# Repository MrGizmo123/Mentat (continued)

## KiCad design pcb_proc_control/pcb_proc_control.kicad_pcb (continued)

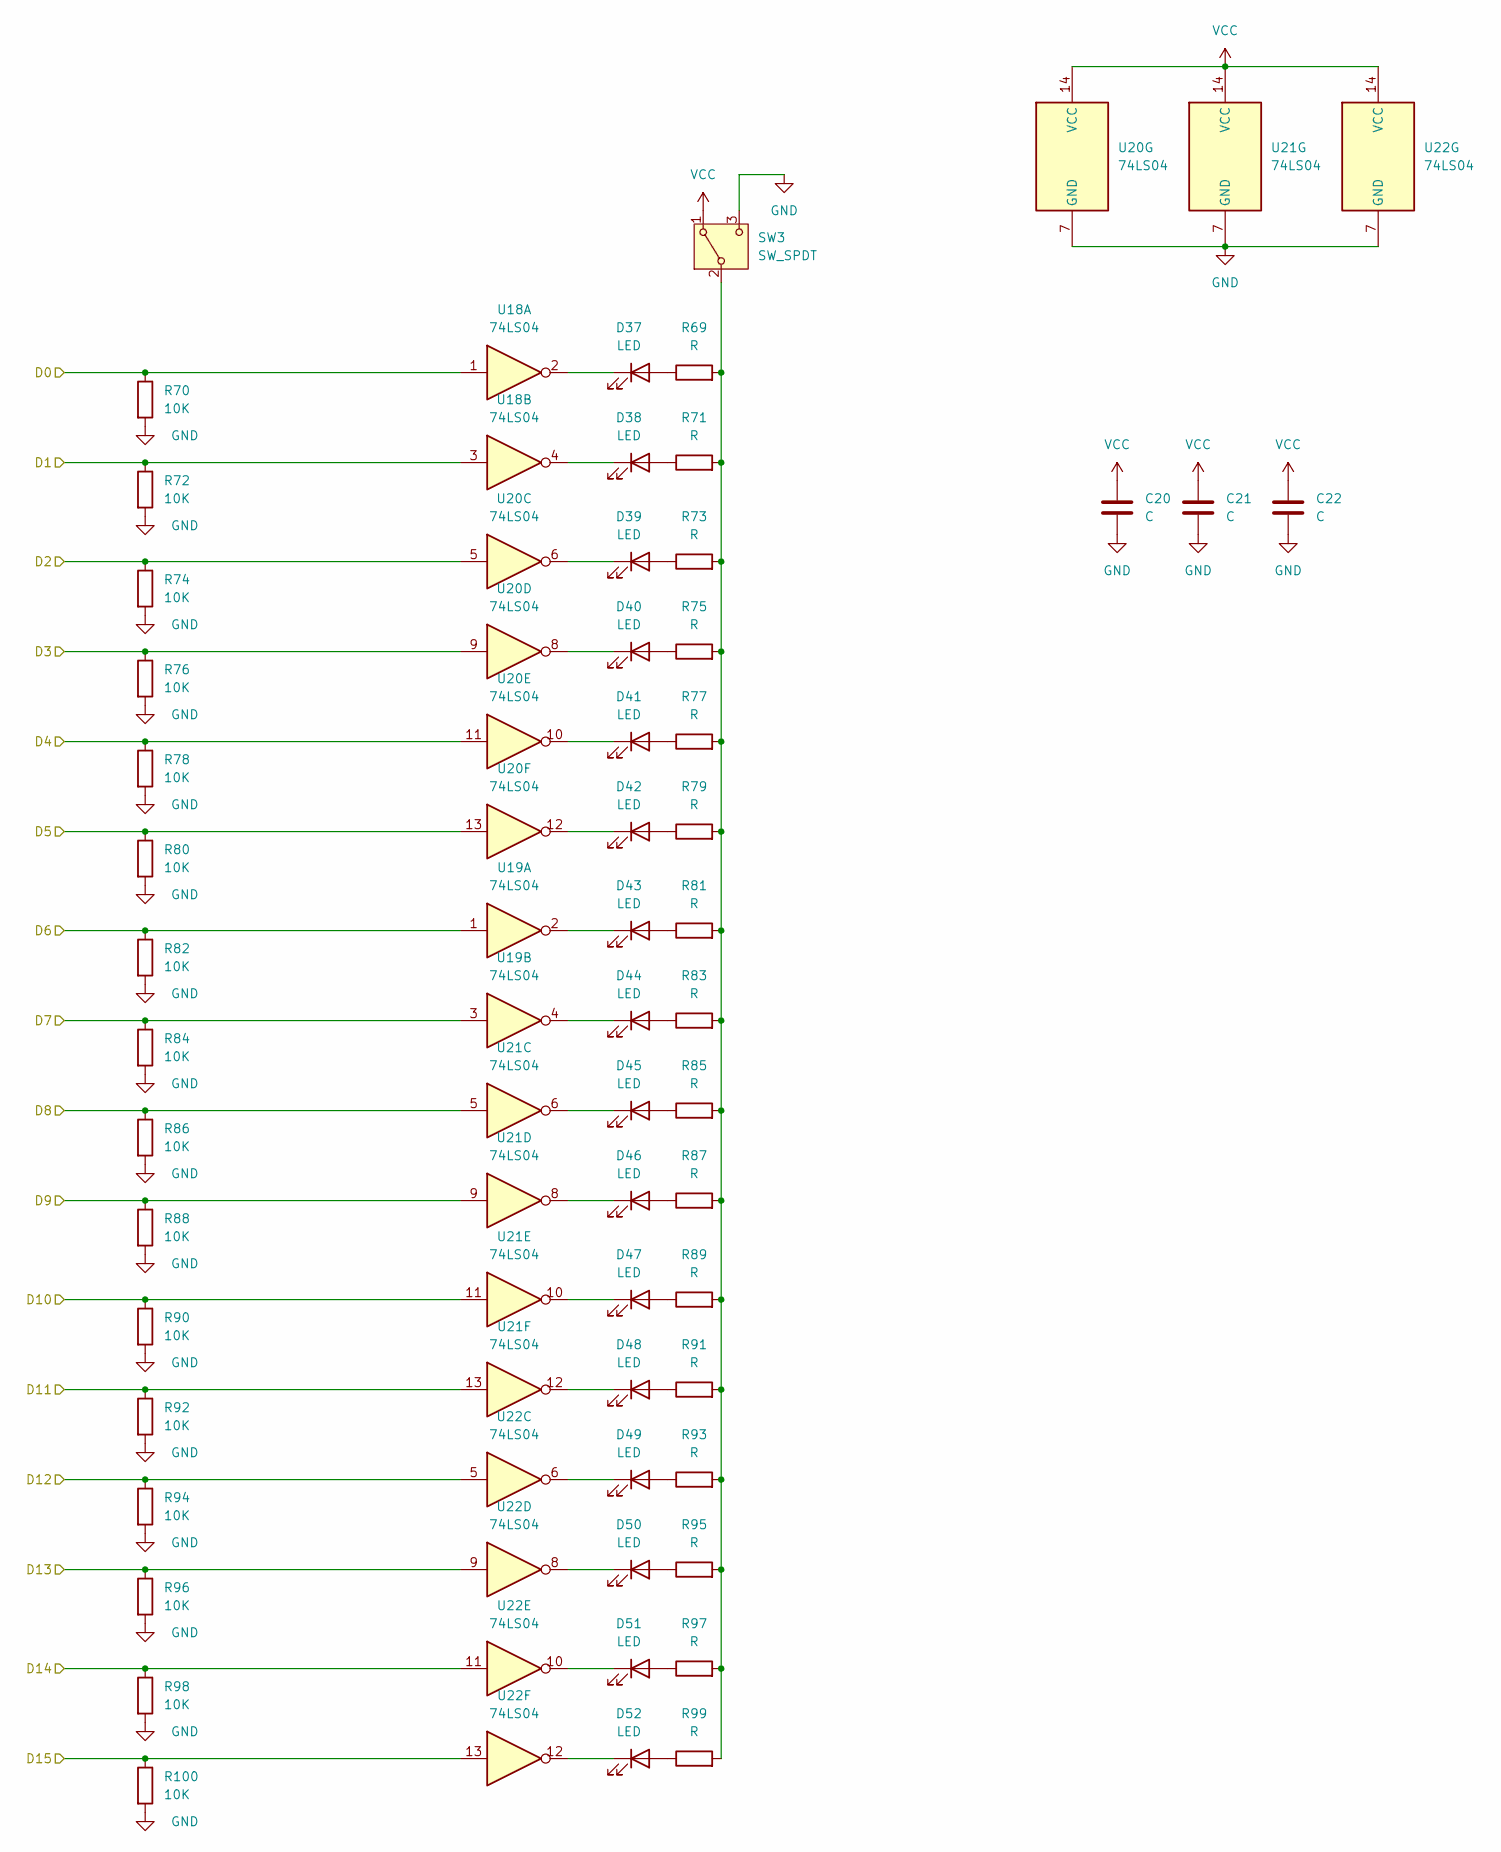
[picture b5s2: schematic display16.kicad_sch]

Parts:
C20, C21, C22: C; C_0805_2012Metric
D37, D38, D39, D40, D41, D42, D43, D44, D45, D46, D47, D48, D49, D50, D51, D52: LED; LED_Rectangular_W5.0mm_H2.0mm
R69, R71, R73, R75, R77, R79, R81, R83, R85, R87, R89, R91, R93, R95, R97, R99: R; R_0805_2012Metric
R70, R72, R74, R76, R78, R80, R82, R84, R86, R88, R90, R92, R94, R96, R98, R100: 10K; R_0805_2012Metric
SW3: SW_SPDT; SW_E-Switch_EG1271_SPDT
U18, U19, U20, U21, U22: 74LS04; DIP-14_W7.62mm_Socket_LongPads

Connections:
/Display3/D0: R70.1, U18.1; also elsewhere on the board
/Display3/D1: R72.1, U18.3; also elsewhere on the board
/Display3/D2: R74.1, U20.5; also elsewhere on the board
/Display3/D3: R76.1, U20.9; also elsewhere on the board
/Display3/D4: R78.1, U20.11; also elsewhere on the board
/Display3/D5: R80.1, U20.13; also elsewhere on the board
/Display3/D6: R82.1, U19.1; also elsewhere on the board
/Display3/D7: R84.1, U19.3; also elsewhere on the board
/Display3/D8: R86.1, U21.5; also elsewhere on the board
/Display3/D9: R88.1, U21.9; also elsewhere on the board
/Display3/D10: R90.1, U21.11; also elsewhere on the board
/Display3/D11: R92.1, U21.13; also elsewhere on the board
/Display3/D12: R94.1, U22.5
/Display3/D13: R96.1, U22.9
/Display3/D14: R98.1, U22.11
/Display3/D15: R100.1, U22.13
/Display4/D8: U18.5; also elsewhere on the board
/Display4/D9: U18.9; also elsewhere on the board
/Display4/D10: U18.11; also elsewhere on the board
/Display4/D11: U18.13; also elsewhere on the board
/Display4/D12: U19.5; also elsewhere on the board
/Display4/D13: U19.9; also elsewhere on the board
/Display4/D14: U19.11; also elsewhere on the board
/Display4/D15: U19.13; also elsewhere on the board
GND: C20.2, C21.2, C22.2, R70.2, R72.2, R74.2, R76.2, R78.2, R80.2, R82.2, R84.2, R86.2, R88.2, R90.2, R92.2, R94.2, R96.2, R98.2, R100.2, SW3.3 (C), U18.7 (GND), U19.7 (GND), U20.7 (GND), U21.7 (GND), U22.7 (GND); also elsewhere on the board
unnamed 106: U18.6; also elsewhere on the board
unnamed 108: U18.8; also elsewhere on the board
unnamed 110: U18.10; also elsewhere on the board
unnamed 112: U18.12; also elsewhere on the board
unnamed 114: U19.6; also elsewhere on the board
unnamed 116: U19.8; also elsewhere on the board
unnamed 118: U19.10; also elsewhere on the board
unnamed 120: U19.12; also elsewhere on the board
unnamed: D37.2 (A), R69.1
unnamed: D37.1 (K), U18.2
unnamed: D38.2 (A), R71.1
unnamed: D38.1 (K), U18.4
unnamed: D39.2 (A), R73.1
unnamed: D39.1 (K), U20.6
unnamed: D40.2 (A), R75.1
unnamed: D40.1 (K), U20.8
unnamed: D41.2 (A), R77.1
unnamed: D41.1 (K), U20.10
unnamed: D42.2 (A), R79.1
unnamed: D42.1 (K), U20.12
unnamed: D43.2 (A), R81.1
unnamed: D43.1 (K), U19.2
unnamed: D44.2 (A), R83.1
unnamed: D44.1 (K), U19.4
unnamed: D45.2 (A), R85.1
unnamed: D45.1 (K), U21.6
unnamed: D46.2 (A), R87.1
unnamed: D46.1 (K), U21.8
unnamed: D47.2 (A), R89.1
unnamed: D47.1 (K), U21.10
unnamed: D48.2 (A), R91.1
unnamed: D48.1 (K), U21.12
unnamed: D49.2 (A), R93.1
unnamed: D49.1 (K), U22.6
unnamed: D50.2 (A), R95.1
unnamed: D50.1 (K), U22.8
unnamed: D51.2 (A), R97.1
unnamed: D51.1 (K), U22.10
unnamed: D52.2 (A), R99.1
unnamed: D52.1 (K), U22.12
unnamed: R69.2, R71.2, R73.2, R75.2, R77.2, R79.2, R81.2, R83.2, R85.2, R87.2, R89.2, R91.2, R93.2, R95.2, R97.2, R99.2, SW3.2 (B)
VCC: C20.1, C21.1, C22.1, SW3.1 (A), U18.14 (VCC), U19.14 (VCC), U20.14 (VCC), U21.14 (VCC), U22.14 (VCC); also elsewhere on the board

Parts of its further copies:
C14, C15, C16, C17, C18, C19: C; C_0805_2012Metric
D5, D6, D7, D8, D9, D10, D11, D12, D13, D14, D15, D16, D17, D18, D19, D20, D21, D22, D23, D24, D25, D26, D27, D28, D29, D30, D31, D32, D33, D34, D35, D36: LED; LED_Rectangular_W5.0mm_H2.0mm
R5, R7, R9, R11, R13, R15, R17, R19, R21, R23, R25, R27, R29, R31, R33, R35, R37, R39, R41, R43, R45, R47, R49, R51, R53, R55, R57, R59, R61, R63, R65, R67: R; R_0805_2012Metric
R6, R8, R10, R12, R14, R16, R18, R20, R22, R24, R26, R28, R30, R32, R34, R36, R38, R40, R42, R44, R46, R48, R50, R52, R54, R56, R58, R60, R62, R64, R66, R68: 10K; R_0805_2012Metric
SW1, SW2: SW_SPDT; SW_E-Switch_EG1271_SPDT
U14, U15, U16, U17: 74LS04; DIP-14_W7.62mm_Socket_LongPads

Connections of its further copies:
/Display1/D0: R6.1, U14.1; also elsewhere on the board
/Display1/D1: R8.1, U14.3; also elsewhere on the board
/Display1/D2: R10.1, U14.5; also elsewhere on the board
/Display1/D3: R12.1, U14.9; also elsewhere on the board
/Display1/D4: R14.1, U14.11; also elsewhere on the board
/Display1/D5: R16.1, U14.13; also elsewhere on the board
/Display1/D6: R18.1, U15.1; also elsewhere on the board
/Display1/D7: R20.1, U15.3; also elsewhere on the board
/Display1/D8: R22.1, U15.5; also elsewhere on the board
/Display1/D9: R24.1, U15.9; also elsewhere on the board
/Display1/D10: R26.1, U15.11; also elsewhere on the board
/Display1/D11: R28.1, U15.13; also elsewhere on the board
/Display1/D12: R30.1, U16.5; also elsewhere on the board
/Display1/D13: R32.1, U16.9; also elsewhere on the board
/Display1/D14: R34.1, U16.11; also elsewhere on the board
/Display1/D15: R36.1, U16.13; also elsewhere on the board
/Display4/D0: R38.1, U16.1; also elsewhere on the board
/Display4/D1: R40.1, U16.3; also elsewhere on the board
/Display4/D2: R42.1, U17.5; also elsewhere on the board
/Display4/D3: R44.1, U17.9; also elsewhere on the board
/Display4/D4: R46.1, U17.11; also elsewhere on the board
/Display4/D5: R48.1, U17.13; also elsewhere on the board
/Display4/D6: R50.1, U17.1; also elsewhere on the board
/Display4/D7: R52.1, U17.3; also elsewhere on the board
/Display4/D8: R54.1; also elsewhere on the board
/Display4/D9: R56.1; also elsewhere on the board
/Display4/D10: R58.1; also elsewhere on the board
/Display4/D11: R60.1; also elsewhere on the board
/Display4/D12: R62.1; also elsewhere on the board
/Display4/D13: R64.1; also elsewhere on the board
/Display4/D14: R66.1; also elsewhere on the board
/Display4/D15: R68.1; also elsewhere on the board
GND: C14.2, C15.2, C16.2, C17.2, C18.2, C19.2, R6.2, R8.2, R10.2, R12.2, R14.2, R16.2, R18.2, R20.2, R22.2, R24.2, R26.2, R28.2, R30.2, R32.2, R34.2, R36.2, R38.2, R40.2, R42.2, R44.2, R46.2, R48.2, R50.2, R52.2, R54.2, R56.2, R58.2, R60.2, R62.2, R64.2, R66.2, R68.2, SW1.3 (C), SW2.3 (C), U14.7 (GND), U15.7 (GND), U16.7 (GND), U17.7 (GND); also elsewhere on the board
unnamed: D5.2 (A), R5.1
unnamed: D5.1 (K), U14.2
unnamed: D6.2 (A), R7.1
unnamed: D6.1 (K), U14.4
unnamed: D7.2 (A), R9.1
unnamed: D7.1 (K), U14.6
unnamed: D8.2 (A), R11.1
unnamed: D8.1 (K), U14.8
unnamed: D9.2 (A), R13.1
unnamed: D9.1 (K), U14.10
unnamed: D10.2 (A), R15.1
unnamed: D10.1 (K), U14.12
unnamed: D11.2 (A), R17.1
unnamed: D11.1 (K), U15.2
unnamed: D12.2 (A), R19.1
unnamed: D12.1 (K), U15.4
unnamed: D13.2 (A), R21.1
unnamed: D13.1 (K), U15.6
unnamed: D14.2 (A), R23.1
unnamed: D14.1 (K), U15.8
unnamed: D15.2 (A), R25.1
unnamed: D15.1 (K), U15.10
unnamed: D16.2 (A), R27.1
unnamed: D16.1 (K), U15.12
unnamed: D17.2 (A), R29.1
unnamed: D17.1 (K), U16.6
unnamed: D18.2 (A), R31.1
unnamed: D18.1 (K), U16.8
unnamed: D19.2 (A), R33.1
unnamed: D19.1 (K), U16.10
unnamed: D20.2 (A), R35.1
unnamed: D20.1 (K), U16.12
unnamed: D21.2 (A), R37.1
unnamed: D21.1 (K), U16.2
unnamed: D22.2 (A), R39.1
unnamed: D22.1 (K), U16.4
unnamed: D23.2 (A), R41.1
unnamed: D23.1 (K), U17.6
unnamed: D24.2 (A), R43.1
unnamed: D24.1 (K), U17.8
unnamed: D25.2 (A), R45.1
unnamed: D25.1 (K), U17.10
unnamed: D26.2 (A), R47.1
unnamed: D26.1 (K), U17.12
unnamed: D27.2 (A), R49.1
unnamed: D27.1 (K), U17.2
unnamed: D28.2 (A), R51.1
unnamed: D28.1 (K), U17.4
unnamed: D29.2 (A), R53.1
unnamed 106: D29.1 (K); also elsewhere on the board
unnamed: D30.2 (A), R55.1
unnamed 108: D30.1 (K); also elsewhere on the board
unnamed: D31.2 (A), R57.1
unnamed 110: D31.1 (K); also elsewhere on the board
unnamed: D32.2 (A), R59.1
unnamed 112: D32.1 (K); also elsewhere on the board
unnamed: D33.2 (A), R61.1
unnamed 114: D33.1 (K); also elsewhere on the board
unnamed: D34.2 (A), R63.1
unnamed 116: D34.1 (K); also elsewhere on the board
unnamed: D35.2 (A), R65.1
unnamed 118: D35.1 (K); also elsewhere on the board
unnamed: D36.2 (A), R67.1
unnamed 120: D36.1 (K); also elsewhere on the board
unnamed: R5.2, R7.2, R9.2, R11.2, R13.2, R15.2, R17.2, R19.2, R21.2, R23.2, R25.2, R27.2, R29.2, R31.2, R33.2, R35.2, SW1.2 (B)
unnamed: R37.2, R39.2, R41.2, R43.2, R45.2, R47.2, R49.2, R51.2, R53.2, R55.2, R57.2, R59.2, R61.2, R63.2, R65.2, R67.2, SW2.2 (B)
VCC: C14.1, C15.1, C16.1, C17.1, C18.1, C19.1, SW1.1 (A), SW2.1 (A), U14.14 (VCC), U15.14 (VCC), U16.14 (VCC), U17.14 (VCC); also elsewhere on the board

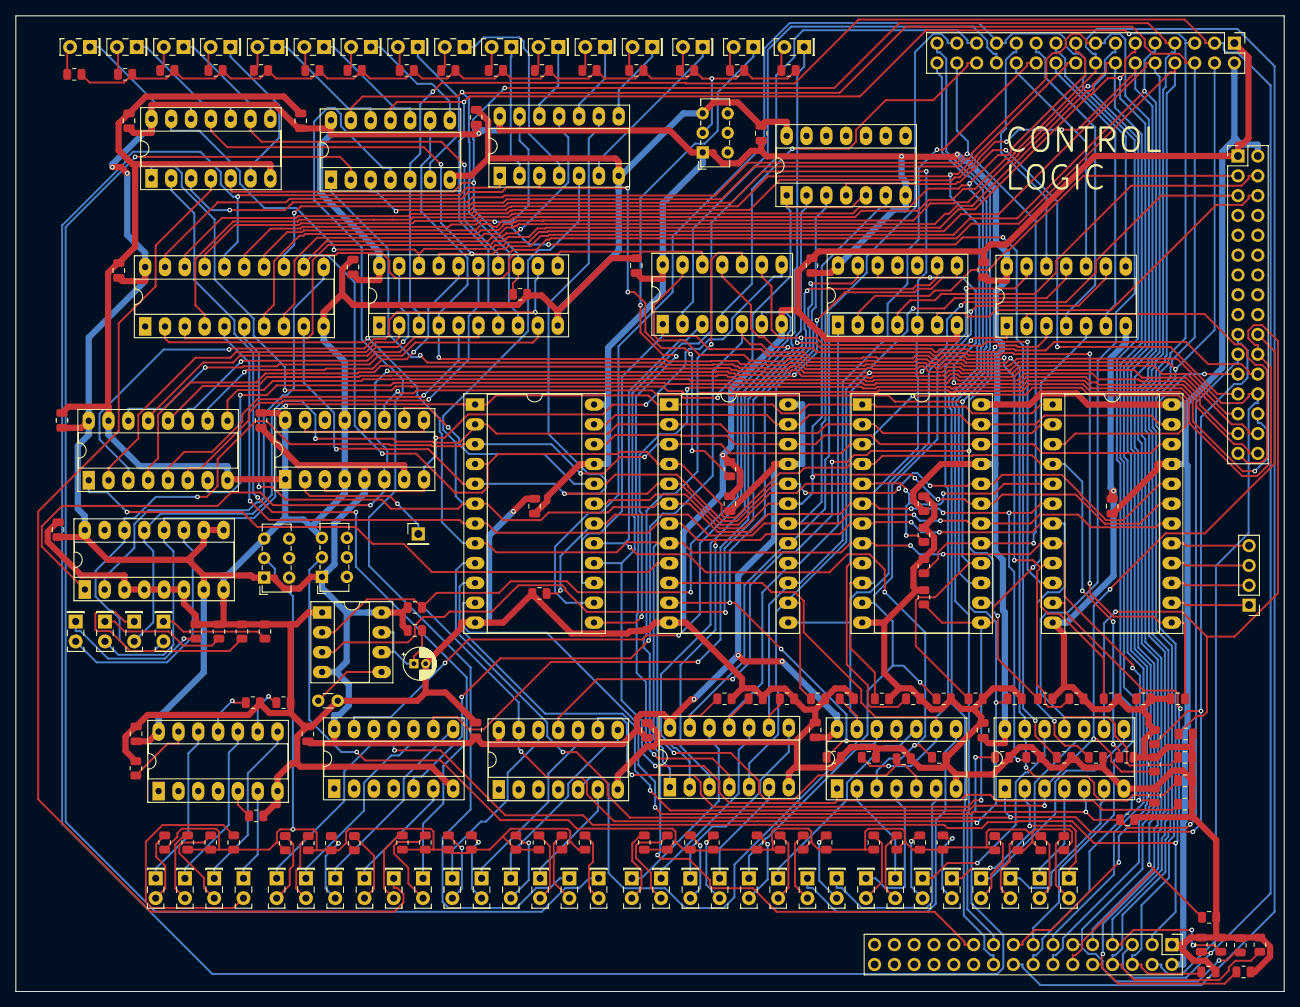
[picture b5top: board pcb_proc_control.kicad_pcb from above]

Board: 2 copper layers, 162.5 x 125.0 mm, 210 parts (0 on the bottom side), 212 nets.

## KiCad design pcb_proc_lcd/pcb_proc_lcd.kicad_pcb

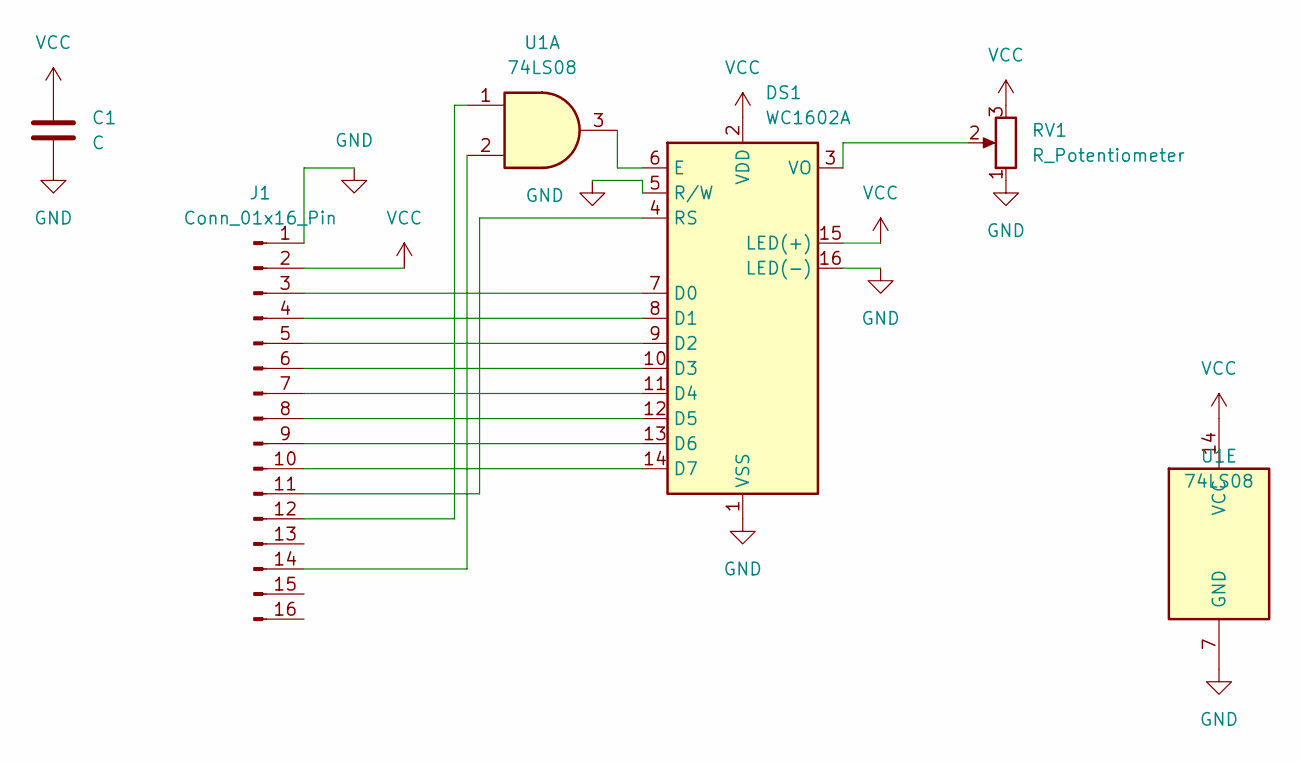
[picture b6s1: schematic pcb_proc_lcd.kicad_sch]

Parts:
C1: C; C_0805_2012Metric
DS1: WC1602A
J1: Conn_01x16_Pin; PinHeader_1x16_P2.54mm_Vertical
RV1: R_Potentiometer; Potentiometer_Vishay_T93YA_Vertical
U1: 74LS08; DIP-14_W7.62mm_Socket_LongPads

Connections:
GND: C1.2, DS1.1 (VSS), DS1.5 (R/W), DS1.16 (LED(-)), J1.1, RV1.1, U1.7 (GND)
unnamed: DS1.7 (D0), J1.3
unnamed: DS1.8 (D1), J1.4
unnamed: DS1.9 (D2), J1.5
unnamed: DS1.10 (D3), J1.6
unnamed: DS1.11 (D4), J1.7
unnamed: DS1.12 (D5), J1.8
unnamed: DS1.13 (D6), J1.9
unnamed: DS1.14 (D7), J1.10
unnamed: DS1.6 (E), U1.3
unnamed: DS1.4 (RS), J1.11
unnamed: DS1.3 (VO), RV1.2
unnamed: J1.12, U1.1
unnamed: J1.14, U1.2
VCC: C1.1, DS1.2 (VDD), DS1.15 (LED(+)), J1.2, RV1.3, U1.14 (VCC)

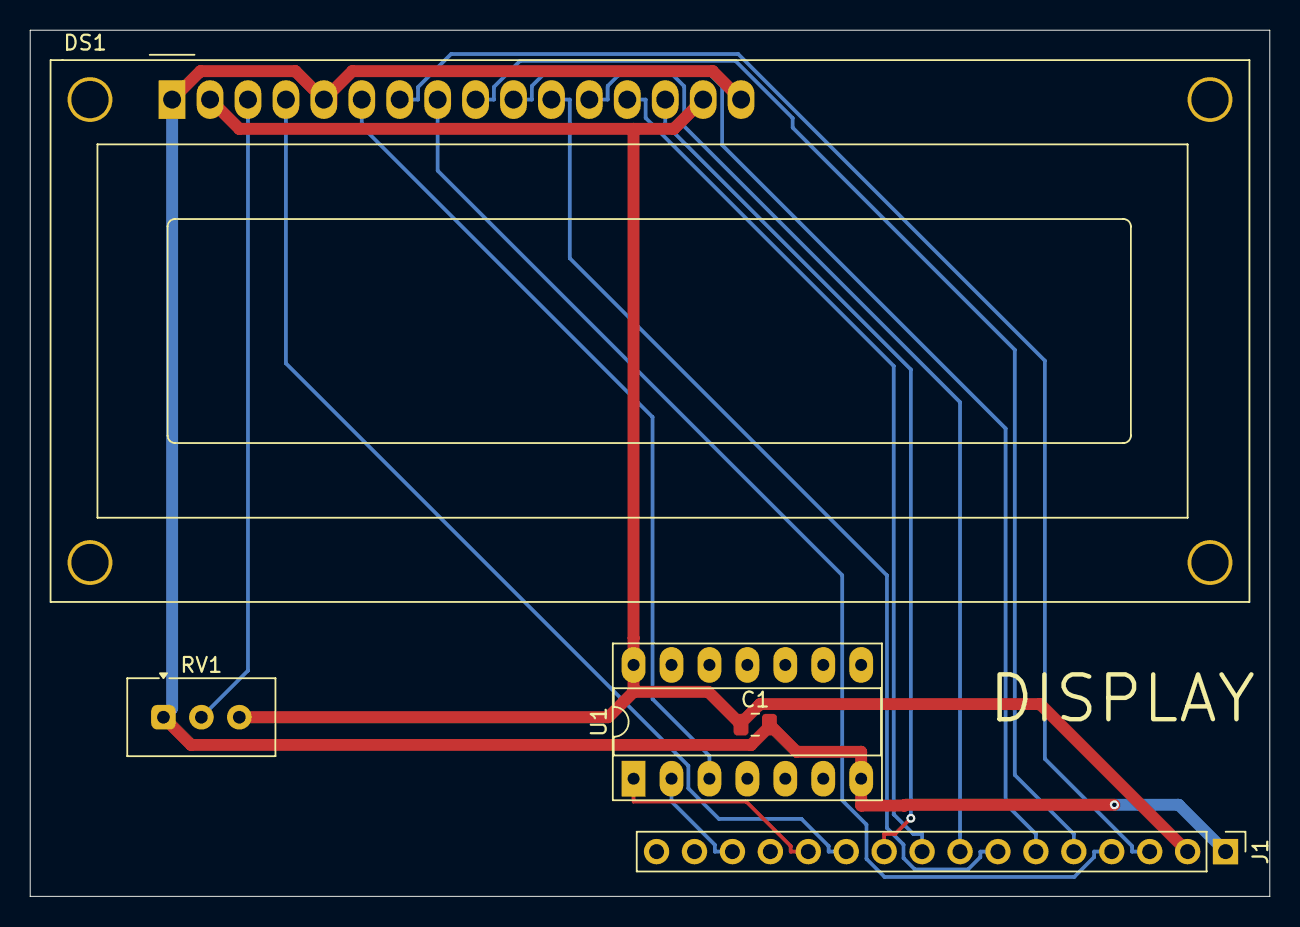
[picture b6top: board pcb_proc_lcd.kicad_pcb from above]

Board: 2 copper layers, 83.0 x 58.0 mm, 5 parts (0 on the bottom side), 15 nets.

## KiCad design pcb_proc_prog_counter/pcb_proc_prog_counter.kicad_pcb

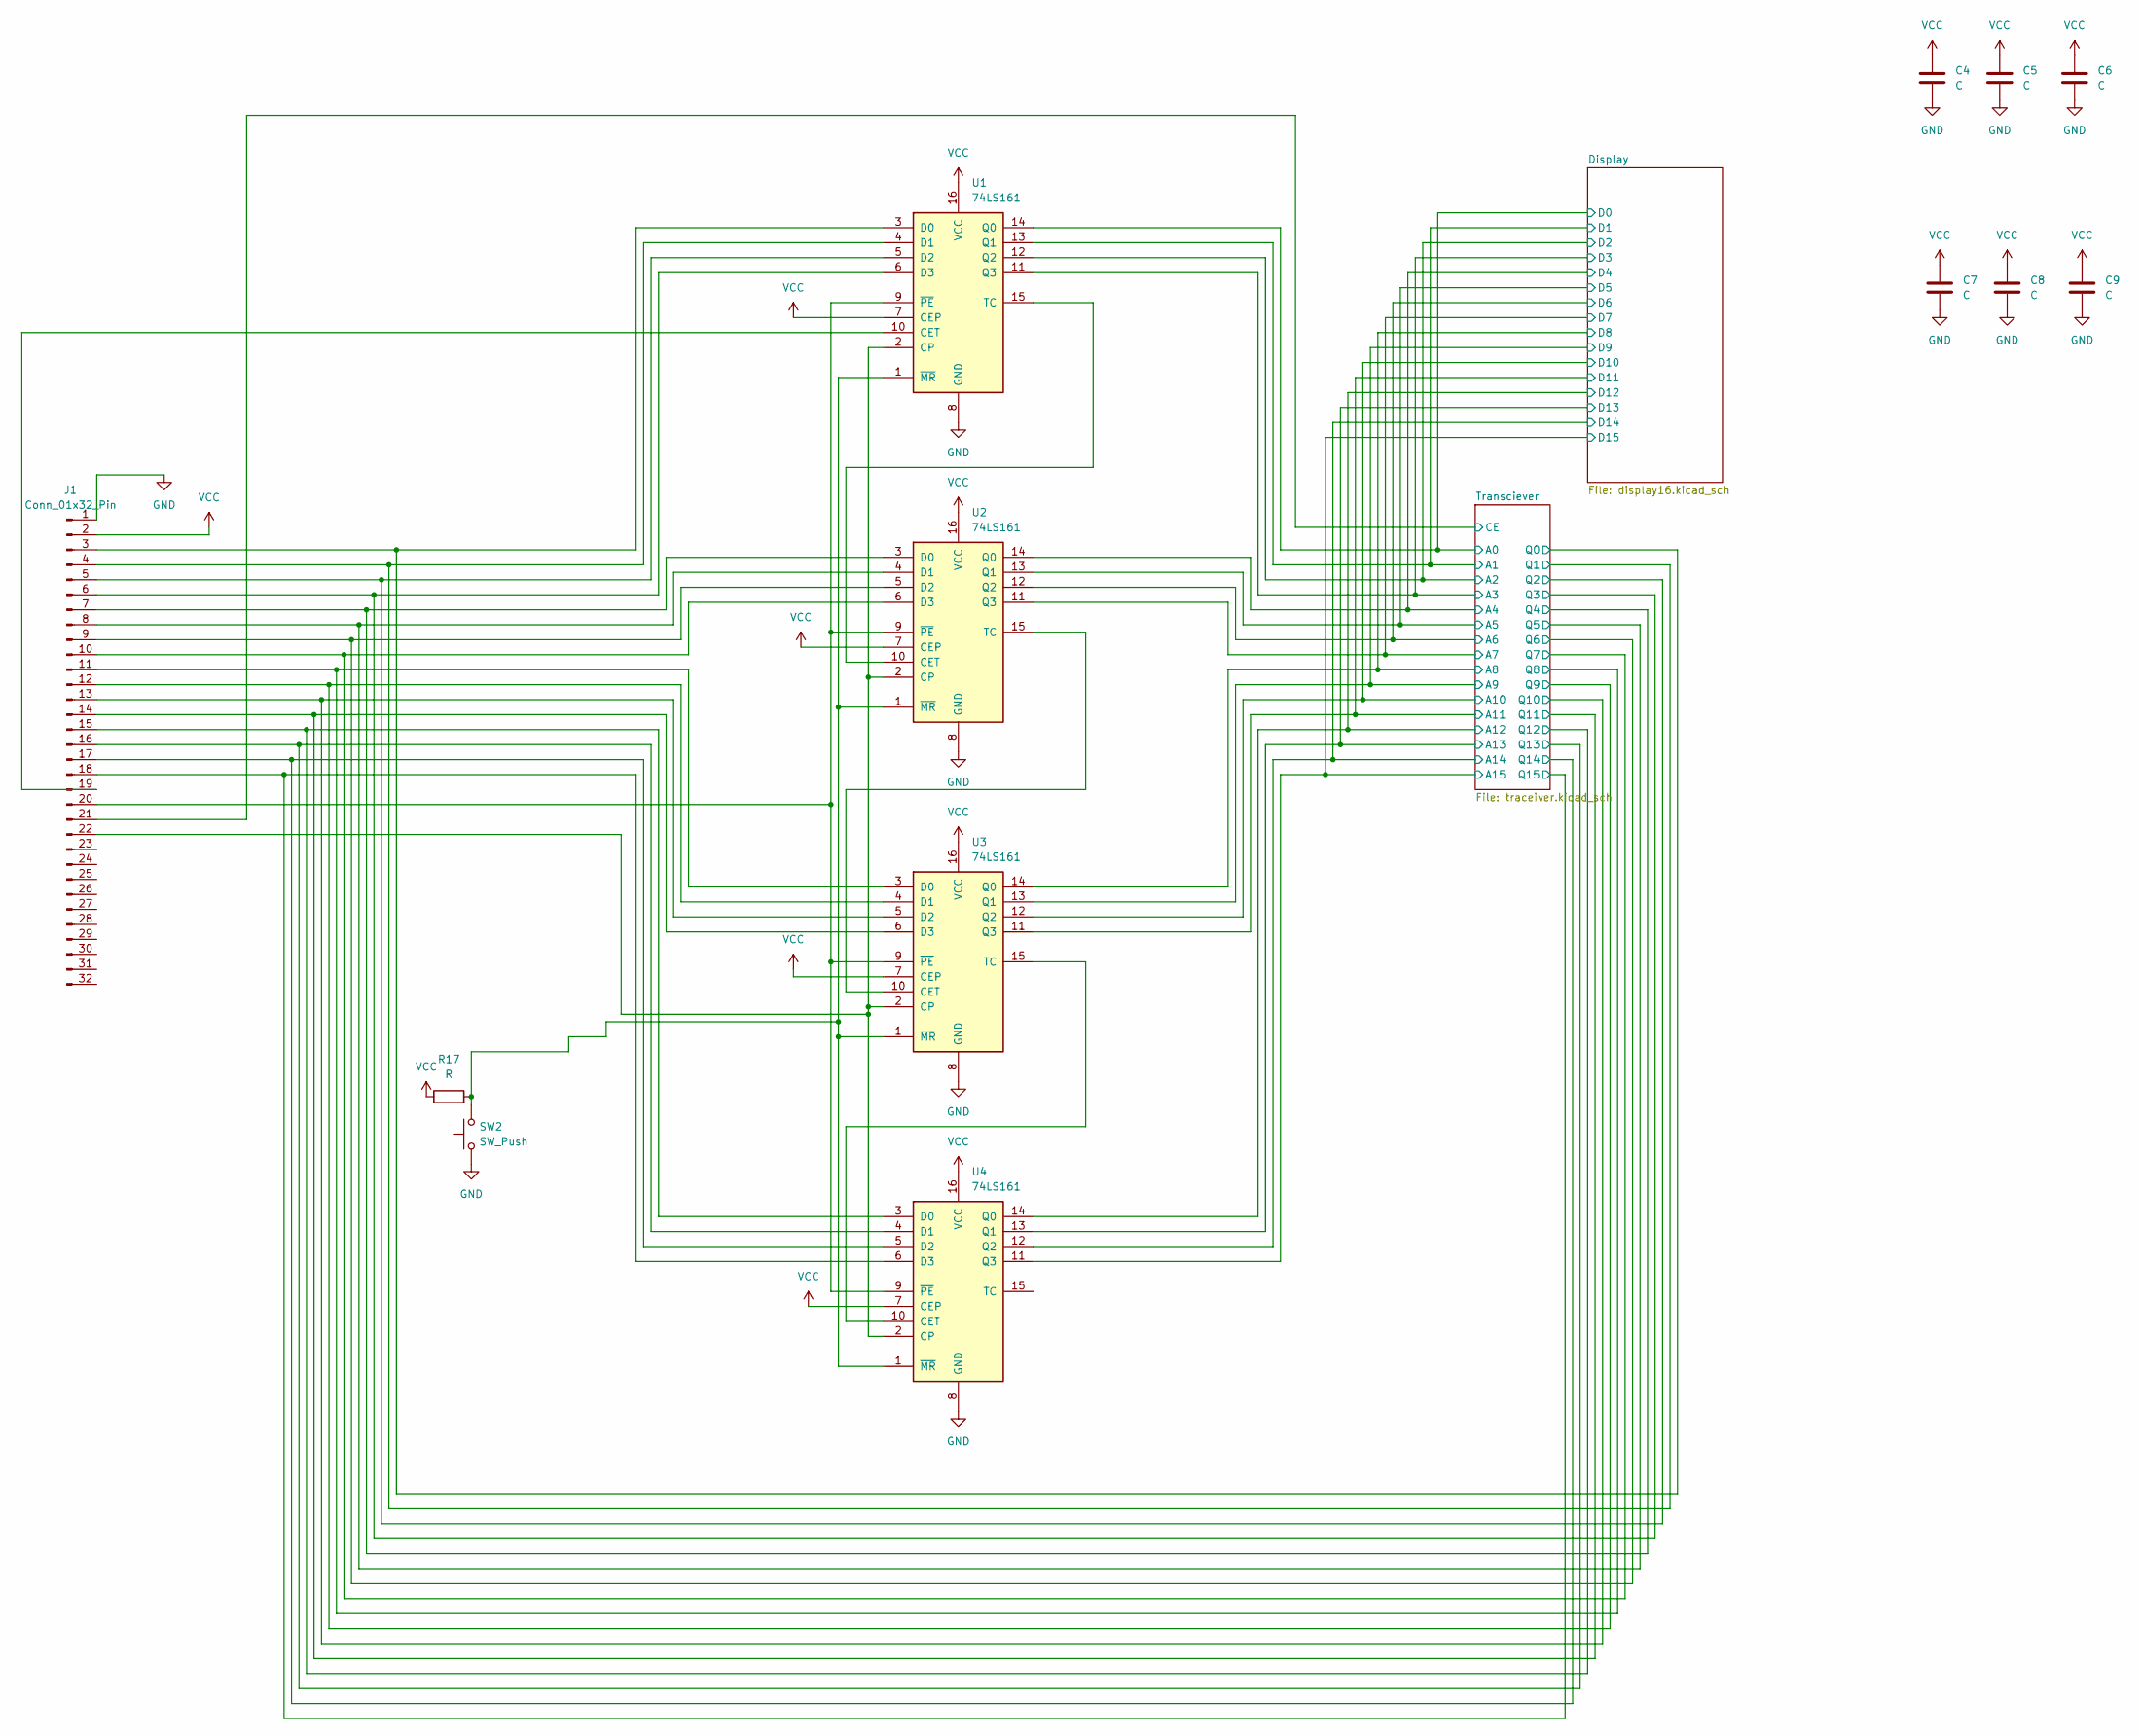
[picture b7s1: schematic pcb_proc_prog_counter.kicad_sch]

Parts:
C4, C5, C6, C7, C8, C9: C; C_0805_2012Metric
J1: Conn_01x32_Pin; PinHeader_2x16_P2.54mm_Vertical
R17: R; R_0805_2012Metric
SW2: SW_Push; SW_PUSH_6mm
U1, U2, U3, U4: 74LS161; DIP-16_W7.62mm_Socket_LongPads

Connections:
/Display/D0: U1.14 (Q0); also elsewhere on the board
/Display/D1: U1.13 (Q1); also elsewhere on the board
/Display/D2: U1.12 (Q2); also elsewhere on the board
/Display/D3: U1.11 (Q3); also elsewhere on the board
/Display/D4: U2.14 (Q0); also elsewhere on the board
/Display/D5: U2.13 (Q1); also elsewhere on the board
/Display/D6: U2.12 (Q2); also elsewhere on the board
/Display/D7: U2.11 (Q3); also elsewhere on the board
/Display/D8: U3.14 (Q0); also elsewhere on the board
/Display/D9: U3.13 (Q1); also elsewhere on the board
/Display/D10: U3.12 (Q2); also elsewhere on the board
/Display/D11: U3.11 (Q3); also elsewhere on the board
/Display/D12: U4.14 (Q0); also elsewhere on the board
/Display/D13: U4.13 (Q1); also elsewhere on the board
/Display/D14: U4.12 (Q2); also elsewhere on the board
/Display/D15: U4.11 (Q3); also elsewhere on the board
/Transciever/CE: J1.21; also elsewhere on the board
/Transciever/Q0: J1.3, U1.3 (D0); also elsewhere on the board
/Transciever/Q1: J1.4, U1.4 (D1); also elsewhere on the board
/Transciever/Q2: J1.5, U1.5 (D2); also elsewhere on the board
/Transciever/Q3: J1.6, U1.6 (D3); also elsewhere on the board
/Transciever/Q4: J1.7, U2.3 (D0); also elsewhere on the board
/Transciever/Q5: J1.8, U2.4 (D1); also elsewhere on the board
/Transciever/Q6: J1.9, U2.5 (D2); also elsewhere on the board
/Transciever/Q7: J1.10, U2.6 (D3); also elsewhere on the board
/Transciever/Q8: J1.11, U3.3 (D0); also elsewhere on the board
/Transciever/Q9: J1.12, U3.4 (D1); also elsewhere on the board
/Transciever/Q10: J1.13, U3.5 (D2); also elsewhere on the board
/Transciever/Q11: J1.14, U3.6 (D3); also elsewhere on the board
/Transciever/Q12: J1.15, U4.3 (D0); also elsewhere on the board
/Transciever/Q13: J1.16, U4.4 (D1); also elsewhere on the board
/Transciever/Q14: J1.17, U4.5 (D2); also elsewhere on the board
/Transciever/Q15: J1.18, U4.6 (D3); also elsewhere on the board
GND: C4.2, C5.2, C6.2, C7.2, C8.2, C9.2, J1.1, SW2.1, U1.8 (GND), U2.8 (GND), U3.8 (GND), U4.8 (GND); also elsewhere on the board
unnamed: J1.19, U1.10 (CET)
unnamed: J1.20, U1.9 (~PE), U2.9 (~PE), U3.9 (~PE), U4.9 (~PE)
unnamed: J1.22, U1.2 (CP), U2.2 (CP), U3.2 (CP), U4.2 (CP)
unnamed: U1.15 (TC), U2.10 (CET)
unnamed: R17.2, SW2.2, U1.1 (~MR), U2.1 (~MR), U3.1 (~MR), U4.1 (~MR)
unnamed: U2.15 (TC), U3.10 (CET)
unnamed: U3.15 (TC), U4.10 (CET)
VCC: C4.1, C5.1, C6.1, C7.1, C8.1, C9.1, J1.2, R17.1, U1.7 (CEP), U1.16 (VCC), U2.7 (CEP), U2.16 (VCC), U3.7 (CEP), U3.16 (VCC), U4.7 (CEP), U4.16 (VCC); also elsewhere on the board

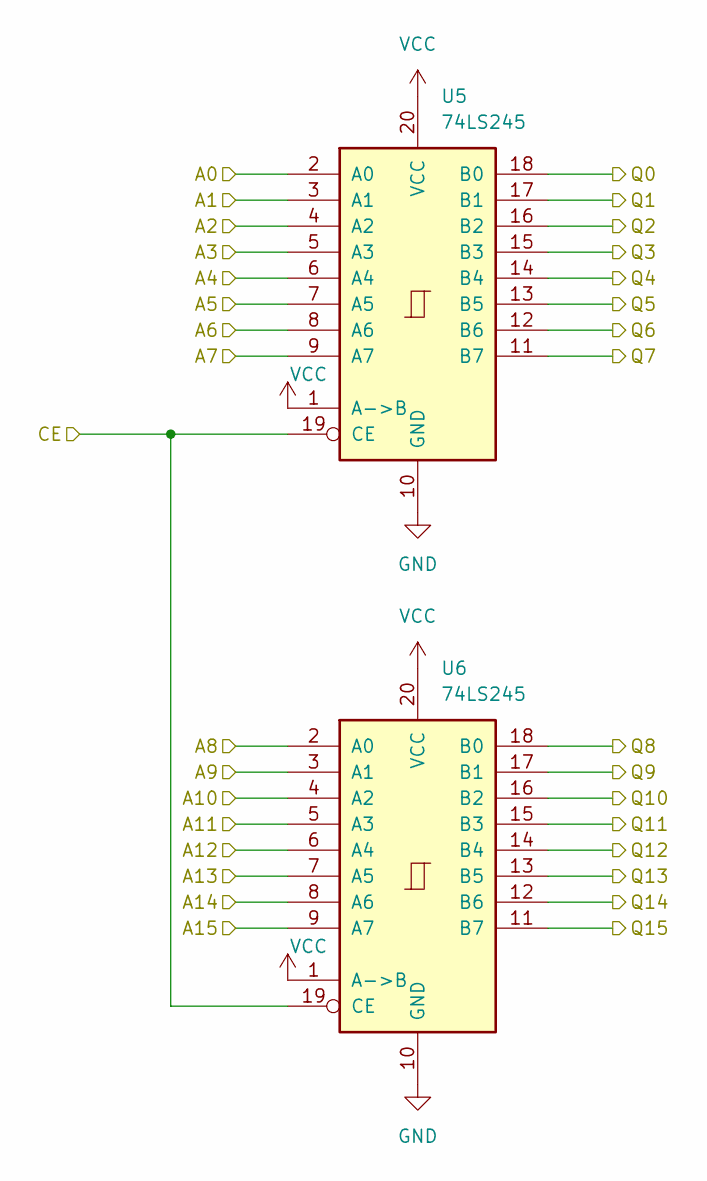
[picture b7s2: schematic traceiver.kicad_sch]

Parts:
U5, U6: 74LS245; DIP-20_W7.62mm_LongPads

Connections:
/Display/D0: U5.2 (A0); also elsewhere on the board
/Display/D1: U5.3 (A1); also elsewhere on the board
/Display/D2: U5.4 (A2); also elsewhere on the board
/Display/D3: U5.5 (A3); also elsewhere on the board
/Display/D4: U5.6 (A4); also elsewhere on the board
/Display/D5: U5.7 (A5); also elsewhere on the board
/Display/D6: U5.8 (A6); also elsewhere on the board
/Display/D7: U5.9 (A7); also elsewhere on the board
/Display/D8: U6.2 (A0); also elsewhere on the board
/Display/D9: U6.3 (A1); also elsewhere on the board
/Display/D10: U6.4 (A2); also elsewhere on the board
/Display/D11: U6.5 (A3); also elsewhere on the board
/Display/D12: U6.6 (A4); also elsewhere on the board
/Display/D13: U6.7 (A5); also elsewhere on the board
/Display/D14: U6.8 (A6); also elsewhere on the board
/Display/D15: U6.9 (A7); also elsewhere on the board
/Transciever/CE: U5.19 (CE), U6.19 (CE); also elsewhere on the board
/Transciever/Q0: U5.18 (B0); also elsewhere on the board
/Transciever/Q1: U5.17 (B1); also elsewhere on the board
/Transciever/Q2: U5.16 (B2); also elsewhere on the board
/Transciever/Q3: U5.15 (B3); also elsewhere on the board
/Transciever/Q4: U5.14 (B4); also elsewhere on the board
/Transciever/Q5: U5.13 (B5); also elsewhere on the board
/Transciever/Q6: U5.12 (B6); also elsewhere on the board
/Transciever/Q7: U5.11 (B7); also elsewhere on the board
/Transciever/Q8: U6.18 (B0); also elsewhere on the board
/Transciever/Q9: U6.17 (B1); also elsewhere on the board
/Transciever/Q10: U6.16 (B2); also elsewhere on the board
/Transciever/Q11: U6.15 (B3); also elsewhere on the board
/Transciever/Q12: U6.14 (B4); also elsewhere on the board
/Transciever/Q13: U6.13 (B5); also elsewhere on the board
/Transciever/Q14: U6.12 (B6); also elsewhere on the board
/Transciever/Q15: U6.11 (B7); also elsewhere on the board
GND: U5.10 (GND), U6.10 (GND); also elsewhere on the board
VCC: U5.1 (A->B), U5.20 (VCC), U6.1 (A->B), U6.20 (VCC); also elsewhere on the board
